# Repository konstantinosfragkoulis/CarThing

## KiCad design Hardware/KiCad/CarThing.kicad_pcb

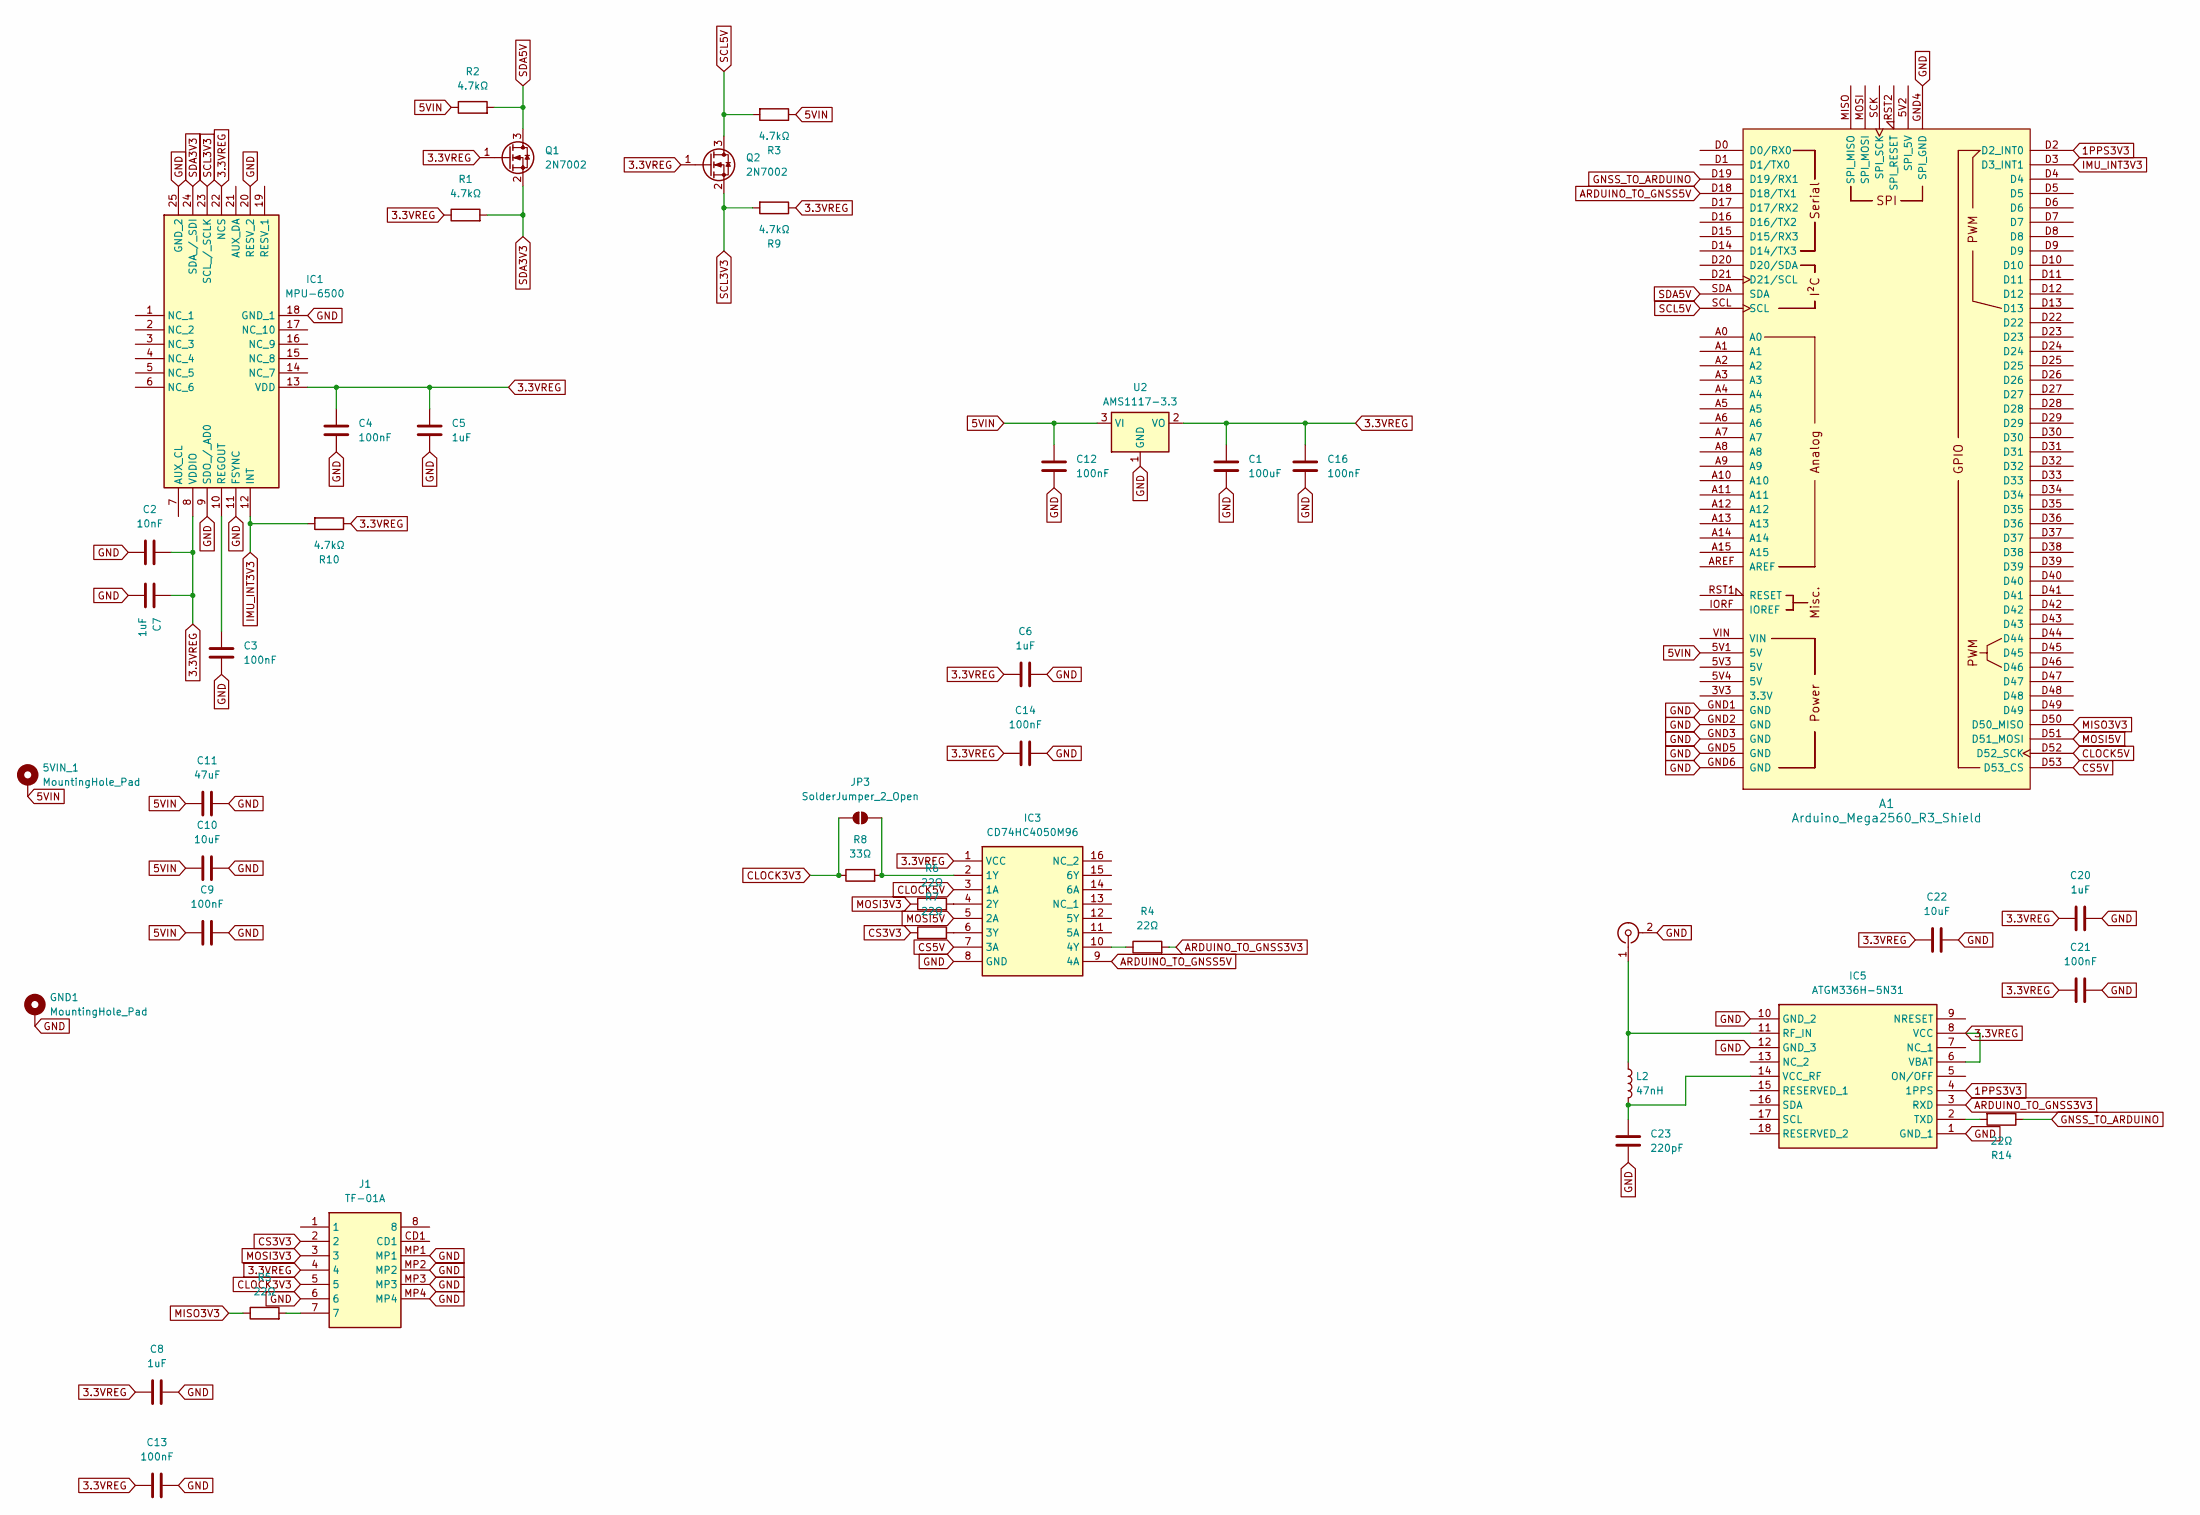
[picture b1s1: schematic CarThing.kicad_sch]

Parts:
5VIN_1: MountingHole_Pad; MountingHole_2.5mm_Pad
A1: Arduino_Mega2560_R3_Shield
C1: 100uF; C_1210_3225Metric
C2: 10nF; C_0402_1005Metric
C3, C4, C9, C12, C13, C14, C16, C21: 100nF; C_0603_1608Metric
C5, C6, C7, C8, C20: 1uF; C_0603_1608Metric
C10, C22: 10uF; C_1206_3216Metric
C11: 47uF; C_Elec_6.3x7.7
C23: 220pF; C_0402_1005Metric
GND1: MountingHole_Pad; MountingHole_2.5mm_Pad
IC1: MPU-6500; QFN40P300X300X95-25N-D; Manufacturer_Part_Number MPU-6500; Mouser Part Number 410-MPU-6500
IC3: CD74HC4050M96; SOIC127P600X175-16N; Manufacturer_Part_Number CD74HC4050M96; Mouser Part Number 595-CD74HC4050M96
IC5: ATGM336H-5N31; ATGM336H5N31; Manufacturer_Part_Number ATGM336H-5N31
J1: TF-01A; TF01A; Manufacturer_Part_Number TF-01A
J2: Conn_Coaxial; U.FL_Hirose_U.FL-R-SMT-1_Vertical
JP3: SolderJumper_2_Open; SolderJumper-2_P1.3mm_Open_RoundedPad1.0x1.5mm
L2: 47nH; L_0603_1608Metric
Q1, Q2: 2N7002; SOT-23
R1, R2, R3, R9, R10: 4.7kΩ; R_0402_1005Metric
R4, R5, R6, R7, R14: 22Ω; R_0402_1005Metric
R8: 33Ω; R_0402_1005Metric
U2: AMS1117-3.3; SOT-223-3_TabPin2

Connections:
1PPS3V3: A1.D2 (D2_INT0), IC5.4 (1PPS)
3.3VREG: C1.1, C2.2, C4.2, C5.2, C6.1, C7.2, C8.1, C13.1, C14.1, C16.1, C20.1, C21.1, C22.1, IC1.8 (VDDIO), IC1.13 (VDD), IC1.22 (NCS), IC3.1 (VCC), IC5.6 (VBAT), IC5.8 (VCC), J1.4, Q1.1 (G), Q2.1 (G), R1.1, R9.1, R10.1, U2.2 (VO)
5VIN: 5VIN_1.1, A1.5V1 (5V), C9.1, C10.1, C11.1, C12.1, R2.1, R3.1, U2.3 (VI)
ARDUINO_TO_GNSS3V3: IC5.3 (RXD), R4.2
ARDUINO_TO_GNSS5V: A1.D18 (D18/TX1), IC3.9 (4A)
CLOCK3V3: J1.5, JP3.2 (B), R8.1
CLOCK5V: A1.D52 (D52_SCK), IC3.3 (1A)
CS3V3: J1.2, R7.1
CS5V: A1.D53 (D53_CS), IC3.7 (3A)
GND: A1.GND1 (GND), A1.GND2 (GND), A1.GND3 (GND), A1.GND4 (SPI_GND), A1.GND5 (GND), A1.GND6 (GND), C1.2, C2.1, C3.1, C4.1, C5.1, C6.2, C7.1, C8.2, C9.2, C10.2, C11.2, C12.2, C13.2, C14.2, C16.2, C20.2, C21.2, C22.2, C23.2, GND1.1, IC1.9 (SDO_/_AD0), IC1.11 (FSYNC), IC1.18 (GND_1), IC1.20 (RESV_2), IC1.25 (GND_2), IC3.8 (GND), IC5.1 (GND_1), IC5.10 (GND_2), IC5.12 (GND_3), J1.6, J1.MP1, J1.MP2, J1.MP3, J1.MP4, J2.2 (Ext), U2.1 (GND)
GNSS_TO_ARDUINO: A1.D19 (D19/RX1), R14.1
IMU_INT3V3: A1.D3 (D3_INT1), IC1.12 (INT), R10.2
MISO3V3: A1.D50 (D50_MISO), R5.1
MOSI3V3: J1.3, R6.1
MOSI5V: A1.D51 (D51_MOSI), IC3.5 (2A)
unnamed: C3.2, IC1.10 (REGOUT)
unnamed: IC3.2 (1Y), JP3.1 (A), R8.2
unnamed: IC3.4 (2Y), R6.2
unnamed: IC3.6 (3Y), R7.2
unnamed: IC3.10 (4Y), R4.1
unnamed: IC5.11 (RF_IN), J2.1 (In), L2.1
unnamed: IC5.2 (TXD), R14.2
unnamed: C23.1, IC5.14 (VCC_RF), L2.2
unnamed: J1.7, R5.2
SCL3V3: IC1.23 (SCL_/_SCLK), Q2.2 (S), R9.2
SCL5V: A1.SCL, Q2.3 (D), R3.2
SDA3V3: IC1.24 (SDA_/_SDI), Q1.2 (S), R1.2
SDA5V: A1.SDA, Q1.3 (D), R2.2

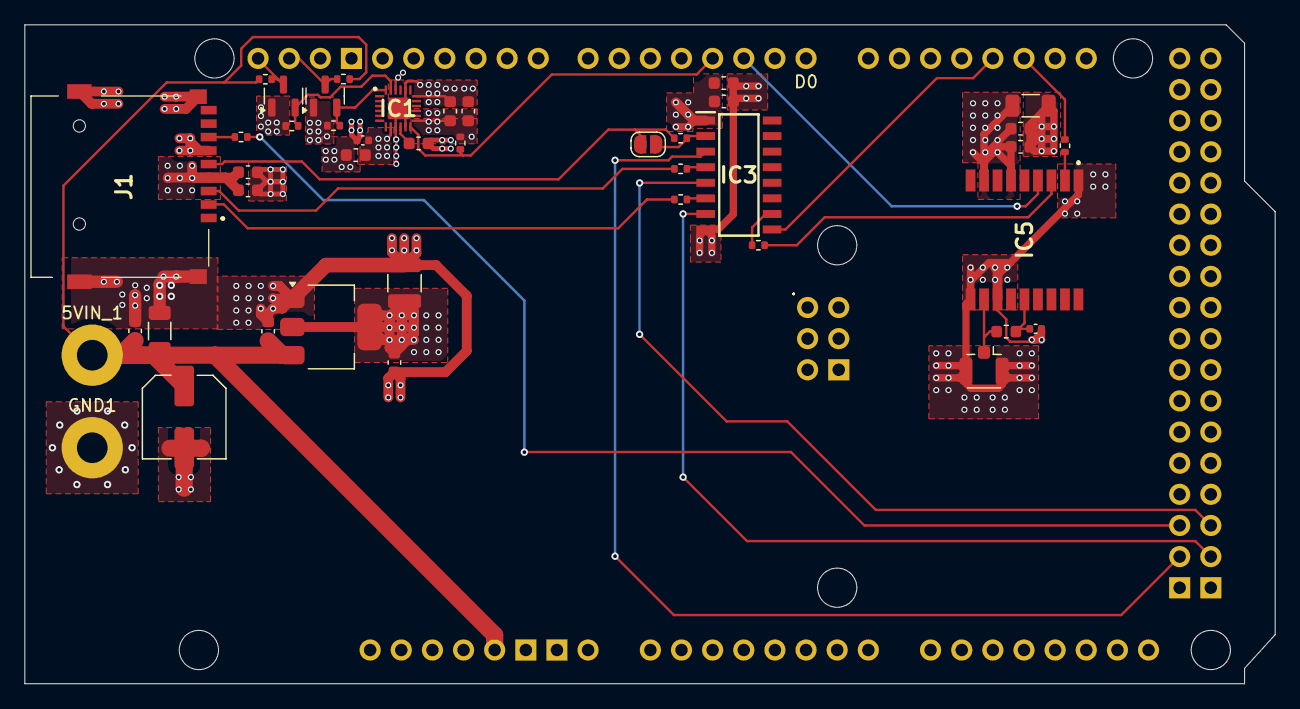
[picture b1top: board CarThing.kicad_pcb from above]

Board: 4 copper layers, 102.0 x 53.8 mm, 43 parts (0 on the bottom side), 28 nets.

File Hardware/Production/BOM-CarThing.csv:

Comment,Designator,Footprint,LCSC,Quantity
CD74HC4050M96,IC3,SOIC127P600X175-16N,C131932,1
10uF,"C10,C22",C_1206_3216Metric,C13585,2
47nH,L2,L_0603_1608Metric,C142358,1
100nF,"C12,C13,C14,C16,C21,C3,C4,C9",C_0603_1608Metric,C14663,8
10nF,C2,C_0402_1005Metric,C15195,1
220pF,C23,C_0402_1005Metric,C1530,1
1uF,"C20,C5,C6,C7,C8",C_0603_1608Metric,C15849,5
100uF,C1,C_1210_3225Metric,C16133,1
22Ω,"R14,R4,R5,R6,R7",R_0402_1005Metric,C25092,5
33Ω,R8,R_0402_1005Metric,C25105,1
4.7kΩ,"R1,R10,R2,R3,R9",R_0402_1005Metric,C25900,5
47uF,C11,C_Elec_6.3x7.7,C3349,1
MPU-6500,IC1,QFN40P300X300X95-25N-D,C50278,1
AMS1117-3.3,U2,SOT-223-3_TabPin2,C6186,1
2N7002,"Q1,Q2",SOT-23,C8545,2
Conn_Coaxial,J2,U.FL_Hirose_U.FL-R-SMT-1_Vertical,C88373,1
ATGM336H-5N31,IC5,ATGM336H5N31,C90770,1
TF-01A,J1,TF01A,C91145,1
Arduino_Mega2560_R3_Shield,A1,Arduino_Mega2560_R3_Shield,,1
